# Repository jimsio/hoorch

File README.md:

an educational multimedia box

HOORCH is a multimedia box for primary school students. HOORCH is a dialect saying that means something like "listen up!".
It consists of a Raspberry Pi 3A+ , 6 RFID-Readers, a microphone, speakers and several LEDs and buttons. It is housed in a laser cutted box with a transparent board top.
We currently have 6 games:
* a storytelling game, where kids can record stories which are then stored for their specific character
* a calculating game
* a game for learning english animal names
* an animal voice guessing game
* an animal orchestra game for learning the animal voices
* a game for learning the parts of a modern instrumental song (e.g. bass line, hi-hat, snare, kick, melody)

Folders:
* . : python program, installation file (installer.sh), 
* [data](data): audio files
* [pcb](pcb): schematics, made with KiCad
* [graphics](graphics): laser cutter files for box, figures. vinylcutter files for cards, graphic files for animal stickers
* [docs](docs): documentation

HOORCH was developed at the University for Teacher Training (PH Wien) in Vienna, Austria.

Also visit our website:
(http://hoorch.phwien.ac.at)

# Installation

see [docs](docs)

# License

Licenced under the CC-BY-NC-SA 4.0 license

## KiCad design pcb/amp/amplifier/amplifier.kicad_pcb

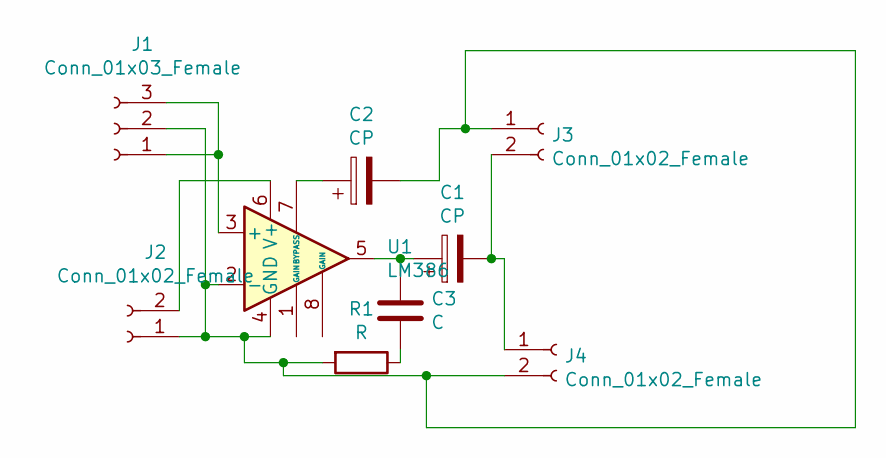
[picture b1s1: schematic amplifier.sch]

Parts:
C1: CP; CP_Radial_D10.0mm_P3.80mm
C2: CP; CP_Radial_D5.0mm_P2.50mm
C3: C; C_Disc_D4.3mm_W1.9mm_P5.00mm
J1: Conn_01x03_Female; PinHeader_1x03_P2.54mm_Vertical
J2, J3, J4: Conn_01x02_Female; PinHeader_1x02_P2.54mm_Vertical
R1: R; R_Axial_DIN0207_L6.3mm_D2.5mm_P10.16mm_Horizontal
U1: LM386; DIP-8_W7.62mm

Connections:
unnamed: C1.1, C3.1, U1.5
unnamed: C1.2, J3.2, J4.1
unnamed: C2.1, U1.7 (BYPASS)
unnamed: C2.2, J1.2, J2.1, J3.1, J4.2, R1.2, U1.2 (-), U1.4 (GND)
unnamed: C3.2, R1.1
unnamed: J1.1, J1.3, U1.3 (+)
unnamed: J2.2, U1.6 (V+)

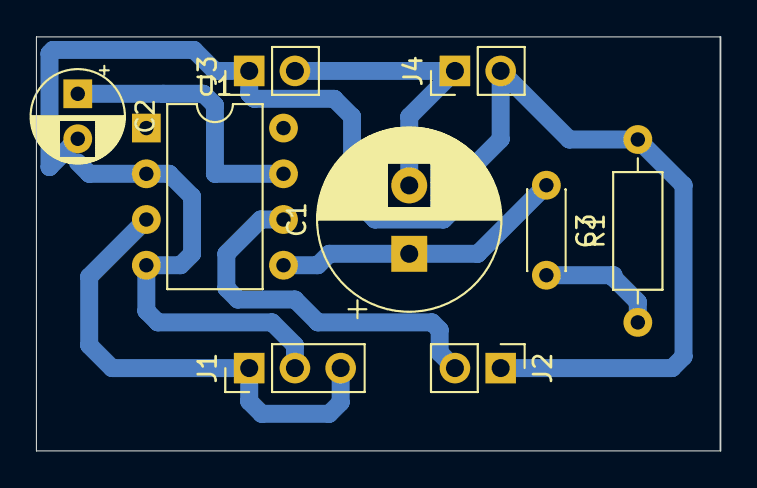
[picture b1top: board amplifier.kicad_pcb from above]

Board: 2 copper layers, 38.0 x 23.0 mm, 9 parts (0 on the bottom side), 7 nets.

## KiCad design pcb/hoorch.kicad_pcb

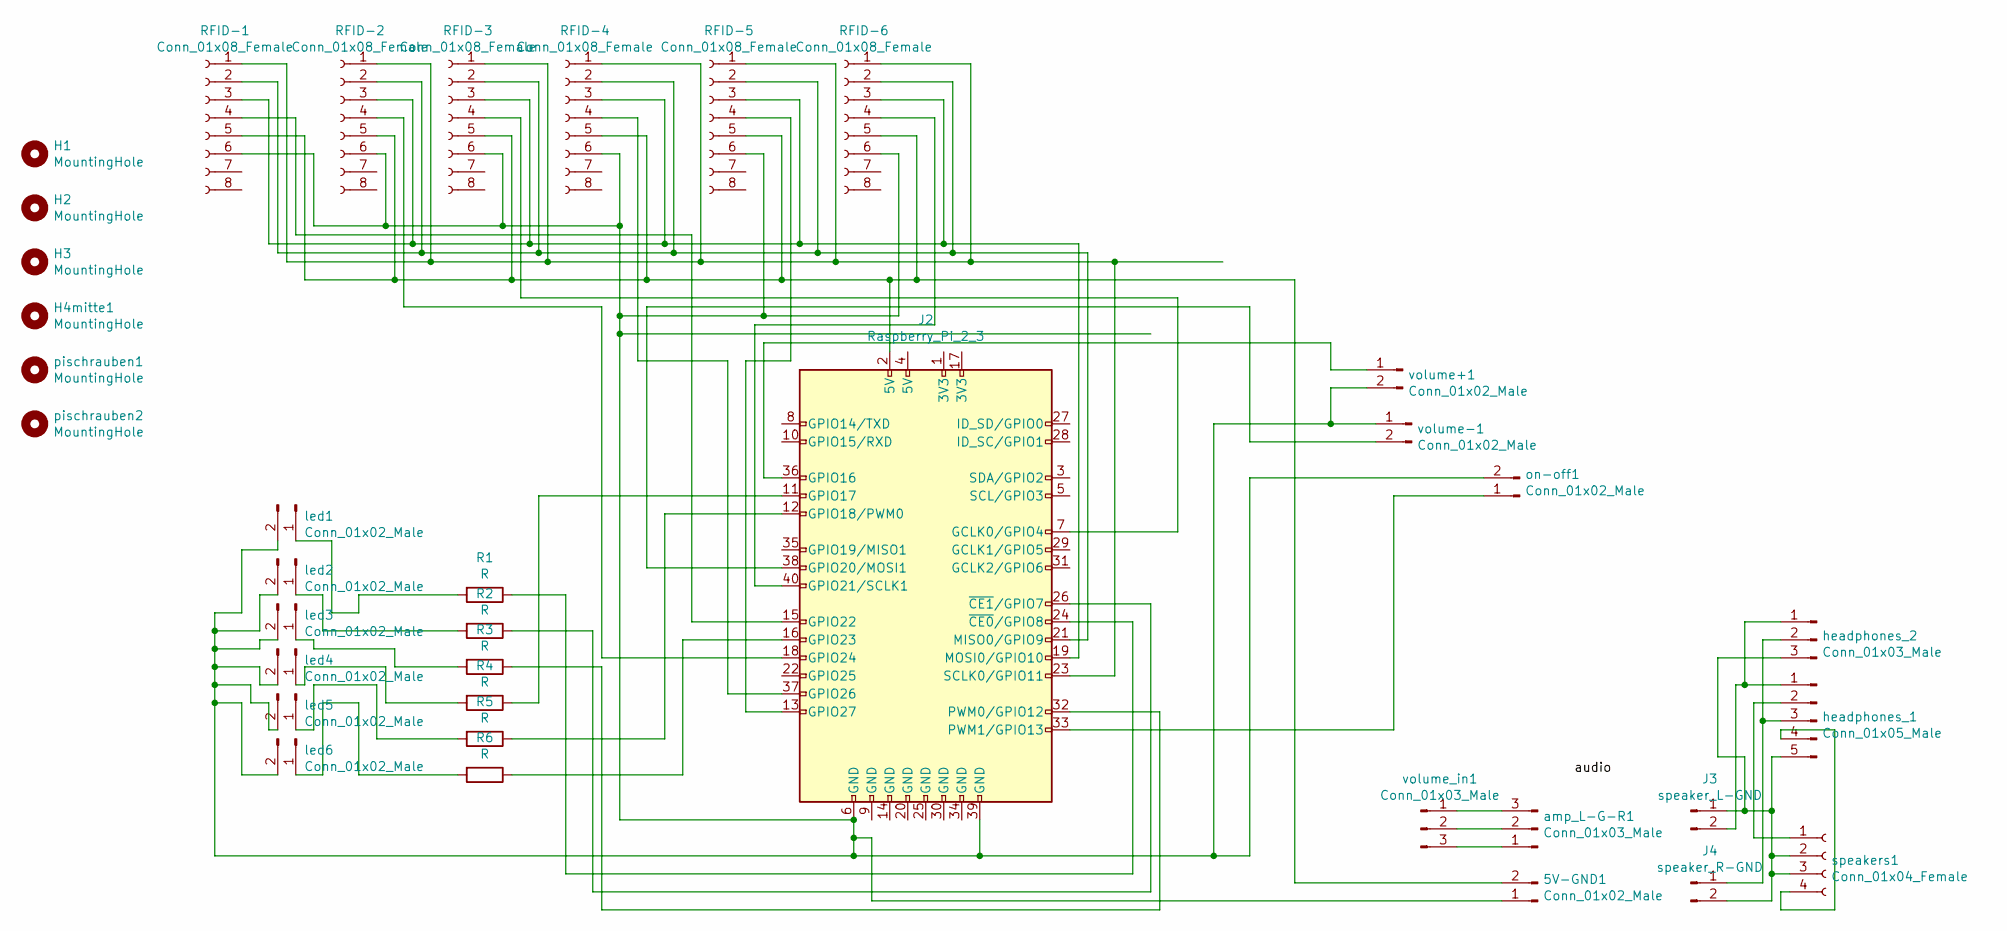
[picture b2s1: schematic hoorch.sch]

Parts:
5V-GND1: Conn_01x02_Male; PinHeader_1x02_P2.54mm_Vertical
H1, H2, H3: MountingHole; MountingHole_4.3mm_M4
H4mitte1: MountingHole; MountingHole_6.4mm_M6
J2: Raspberry_Pi_2_3; PinSocket_2x20_P2.54mm_Vertical
J3: speaker_L-GND; PinSocket_1x02_P2.54mm_Vertical
J4: speaker_R-GND; PinSocket_1x02_P2.54mm_Vertical
R1, R2, R3, R4, R5, R6: R; R_Axial_DIN0204_L3.6mm_D1.6mm_P5.08mm_Vertical
RFID-1, RFID-2, RFID-3, RFID-4, RFID-5, RFID-6: Conn_01x08_Female; PinSocket_1x08_P2.54mm_Vertical
amp_L-G-R1: Conn_01x03_Male; PinHeader_1x03_P2.54mm_Vertical
headphones_1: Conn_01x05_Male; PinHeader_1x05_P2.54mm_Vertical
headphones_2: Conn_01x03_Male; PinHeader_1x03_P2.54mm_Vertical
led1, led2, led3, led4, led5, led6: Conn_01x02_Male; PinSocket_1x02_P2.54mm_Vertical
on-off1: Conn_01x02_Male; PinSocket_1x02_P2.54mm_Vertical
pischrauben1, pischrauben2: MountingHole; MountingHole_3.2mm_M3
speakers1: Conn_01x04_Female; JST_EH_B04B-EH-A_1x04_P2.50mm_Vertical
volume+1: Conn_01x02_Male; PinSocket_1x02_P2.54mm_Vertical
volume-1: Conn_01x02_Male; PinSocket_1x02_P2.54mm_Vertical
volume_in1: Conn_01x03_Male; PinSocket_1x03_P2.54mm_Vertical

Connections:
unnamed: 5V-GND1.1, J2.6 (GND), J2.39 (GND), RFID-1.6, RFID-2.6, RFID-3.6, RFID-4.6, RFID-5.6, RFID-6.6, led1.2, led2.2, led3.2, led4.2, led5.2, led6.2, on-off1.2, volume+1.2, volume-1.1
unnamed: 5V-GND1.2, J2.2 (5V), RFID-1.5, RFID-2.5, RFID-3.5, RFID-4.5, RFID-5.5, RFID-6.5
unnamed: J2.7 (GCLK0/GPIO4), RFID-3.4
unnamed: J2.11 (GPIO17), R4.1
unnamed: J2.12 (GPIO18/PWM0), R5.1
unnamed: J2.13 (GPIO27), RFID-5.4
unnamed: J2.15 (GPIO22), RFID-1.4
unnamed: J2.16 (GPIO23), R6.1
unnamed: J2.18 (GPIO24), RFID-2.4
unnamed: J2.19 (MOSI0/GPIO10), RFID-1.3, RFID-2.3, RFID-3.3, RFID-4.3, RFID-5.3, RFID-6.3
unnamed: J2.21 (MISO0/GPIO9), RFID-1.2, RFID-2.2, RFID-3.2, RFID-4.2, RFID-5.2, RFID-6.2
unnamed: J2.23 (SCLK0/GPIO11), RFID-1.1, RFID-2.1, RFID-3.1, RFID-4.1, RFID-5.1, RFID-6.1
unnamed: J2.24 (~CE0~/GPIO8), R1.1
unnamed: J2.26 (~CE1~/GPIO7), R2.1
unnamed: J2.32 (PWM0/GPIO12), R3.1
unnamed: J2.33 (PWM1/GPIO13), on-off1.1
unnamed: J2.36 (GPIO16), volume+1.1
unnamed: J2.37 (GPIO26), RFID-4.4
unnamed: J2.38 (GPIO20/MOSI1), volume-1.2
unnamed: J2.40 (GPIO21/SCLK1), RFID-6.4
unnamed: J3.1, J4.2, headphones_1.5, headphones_2.3, speakers1.2, speakers1.3
unnamed: J3.2, headphones_1.1, headphones_2.1
unnamed: J4.1, headphones_1.3, headphones_2.2
unnamed: R1.2, led1.1
unnamed: R2.2, led2.1
unnamed: R3.2, led3.1
unnamed: R4.2, led4.1
unnamed: R5.2, led5.1
unnamed: R6.2, led6.1
unnamed: amp_L-G-R1.1, volume_in1.3
unnamed: amp_L-G-R1.2, volume_in1.2
unnamed: amp_L-G-R1.3, volume_in1.1
unnamed: headphones_1.2, speakers1.1
unnamed: headphones_1.4, speakers1.4

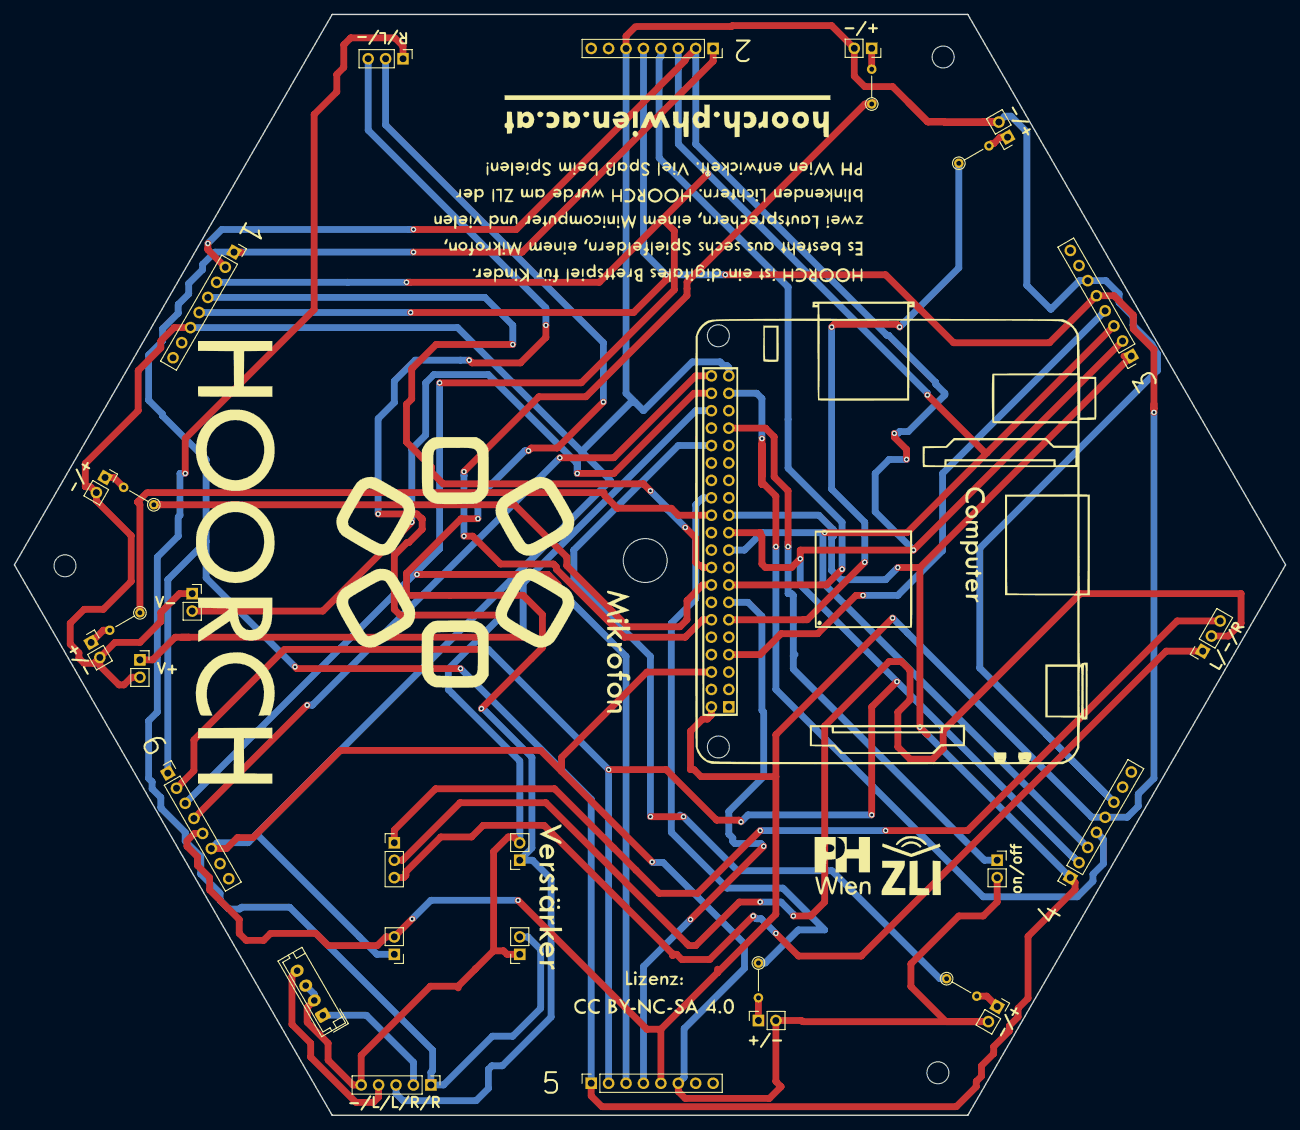
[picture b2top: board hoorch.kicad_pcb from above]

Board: 2 copper layers, 185.3 x 160.5 mm, 36 parts (1 on the bottom side), 34 nets.

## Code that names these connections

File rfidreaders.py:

#!/usr/bin/env python3
# -*- coding: UTF8 -*-

import time
import threading
import os
#import unicodedata
import board
import busio
from adafruit_pn532.spi import PN532_SPI
from adafruit_pn532.adafruit_pn532 import MIFARE_CMD_AUTH_B
#import digitalio
from digitalio import DigitalInOut
import ndef
import audio

# gpio belegung
# Reader 1: Pin18 - GPIO24
# Reader 2: Pin15 - GPIO22
# Reader 3: Pin7 - GPIO4
# Reader 4: Pin37 - GPIO26
# Reader 5: Pin13 - GPIO27
# Reader 6: Pin36 - GPIO16
reader1_pin = DigitalInOut(board.D24)
reader2_pin = DigitalInOut(board.D22)
reader3_pin = DigitalInOut(board.D4)
reader4_pin = DigitalInOut(board.D26)
reader5_pin = DigitalInOut(board.D27)
reader6_pin = DigitalInOut(board.D16)

readers = []
tags = []
timer = [0, 0, 0, 0, 0, 0]

figures_db = {}  # figure database is a dictionary with tag id and tag name stored, based on predefined figure_db.txt. figure_db.txt is created when configuring HOORCH for the first time (and is based on tag names in figure_ids.txt)
gamer_figures = []  # ritter, koenigin,...
animal_figures = []  # Loewe2, Elefant1, ...

endofmessage = "#"  # chr(35)

read_continuously = True
currently_reading = False

auth_key = b'\xFF\xFF\xFF\xFF\xFF\xFF'


def init():
    print("initialize the rfid readers and figure_db.txt")
    spi = busio.SPI(board.SCK, board.MOSI, board.MISO)

    readers.append(PN532_SPI(spi, reader1_pin, debug=False))
    readers.append(PN532_SPI(spi, reader2_pin, debug=False))
    readers.append(PN532_SPI(spi, reader3_pin, debug=False))
    readers.append(PN532_SPI(spi, reader4_pin, debug=False))
    readers.append(PN532_SPI(spi, reader5_pin, debug=False))
    readers.append(PN532_SPI(spi, reader6_pin, debug=False))

    for n, reader in enumerate(readers):
        # ic, ver, rev, support = reader.firmware_version
        # print('Found Reader '+str(n)+' with firmware version: {0}.{1}'.format(ver, rev, support))
        reader.SAM_configuration()
        print('Initialized and configured RFID/NFC reader '+str(n+1))
        tags.append(None)
        time.sleep(0.03)

    # init figure db
    path = "./figure_db.txt"

    if os.path.exists(path):
        with open(path, mode="r", encoding="utf-8") as file:
            figures_id_name = file.readlines()
        
        section = 0

        for uid_name in figures_id_name:
            # empty line means section change
            if uid_name.startswith(";"):
                section += 1
            else:
                (key, val) = uid_name.split(";")
                figures_db[key] = val[:val.find("\n")]

                if section == 2:
                    gamer_figures.append(
                        uid_name[uid_name.find(";")+1:uid_name.find("\n")])
                elif section == 3:
                    animal_figures.append(
                        uid_name[uid_name.find(";")+1:uid_name.find("\n")-1])

    continuous_read()


def continuous_read():
    
    global currently_reading

    for index, r in enumerate(readers):

        mifare = False

        currently_reading = True

        tag_uid = r.read_passive_target(timeout=0.2)
        
        if tag_uid:
            # convert byte_array tag_uid to string id_readable (i.e. 4-7-26-160)
            id_readable = ""
            for counter, number in enumerate(tag_uid):
                if counter < 4:
                    id_readable += str(number)+"-"
                else:
                    id_readable = id_readable[:-1]
                    break

            # mifare id has minus at the end, remove it here
            if id_readable.endswith("-"):
                id_readable = id_readable[:-1]
                mifare = True

            # check if tag id in figure db
            try:
                tag_name = figures_db[id_readable]

            # id_readable is not in figures_db
            except KeyError:
                
                if mifare:
                    tag_name = read_from_mifare(r, tag_uid)
                else:
                    tag_name = read_from_ntag2(r)

                # power down to safe energy, breaks readers?
                r.power_down()
                
                if tag_name == "#error#":
                    continue

                currently_reading = False

                #if tag_name is empty, use id_readable
                if not tag_name:
                    #print("tag is empty, use id_readable")
                    tag_name = id_readable

                # if a figure (i.e. Loewe0 or koenigin) from another game (i.e. as a replacement of a lost one) that is already defined in this game is used
                # add another key value pair to the figures_db database
                elif tag_name in figures_db:
                    figures_db[id_readable] = tag_name       

                else:
                    # else set the unknown figure as a gamer figure with read tag_name
            
                    if tag_name not in gamer_figures:
                        gamer_figures.append(tag_name)
                        print(
                            "added new unknown gamer figure to the temporary gamer_figure list")
                    else:
                        pass
                        #print("unknown gamer figure already in temporary gamer_figure list")

        else:
            tag_name = None

        # keep tags in array for 1 seconds to even out reading errors
        if tag_name is None and timer[index] < time.time():
            tags[index] = tag_name  # None
            timer[index] = 0  # reset timer to 0

        if tag_name is not None:
            timer[index] = time.time()+1
            tags[index] = tag_name
        
        #sleep for 0.2 seconds between readers to avoid heavy power load
        time.sleep(0.2)

    print(tags)

    if read_continuously:
        #only read when not playing or recording audio - shouldnt be done, need it for ending recording
        #while ('play' or 'rec') in subprocess.run(['ps', 'ax'], stdout=subprocess.PIPE).stdout.decode('utf-8'):
            #time.sleep(0.2)

        threading.Timer(0.02, continuous_read).start()
        
def read_from_mifare(reader, tag_uid):
    read_data = bytearray(0)
    
    try:
        #read 16 bytes from blocks 4 and 5
        for i in range(4, 6):
            #print("Authenticating block "+str(i))
                authenticated = reader.mifare_classic_authenticate_block(tag_uid, i, MIFARE_CMD_AUTH_B, auth_key)
                if not authenticated:
                    print("Authentication failed!")
                # Read blocks
                read_data.extend(reader.mifare_classic_read_block(i))
        
        to_decode = read_data[2:read_data.find(b'\xfe')]
        return list(ndef.message_decoder(to_decode))[0].text
    
    except TypeError:
        print("Error while reading RFID-tag content. Tag was probably removed before reading was completed.")
        # Die Figur konnte nicht erkannt werden. Lass sie länger auf dem Feld stehen.
        audio.play_full("TTS", 199)

        return "#error#"
    
    except ndef.record.DecodeError as e:
        print("ndeflib Error while decoding")
        print(e)

        return "error#"

def read_from_ntag2(reader):
    read_data = bytearray(0)
    
    #read 4 bytes from blocks 4-11
    try:
        for i in range(4, 12):
            read_data.extend(reader.ntag2xx_read_block(i))
        to_decode = read_data[2:read_data.find(b'\xfe')]
    
        return list(ndef.message_decoder(to_decode))[0].text

    # if tag was removed before it was properly read
    except TypeError:
        print("Error while reading RFID-tag content. Tag was probably removed before reading was completed.")
        # Die Figur konnte nicht erkannt werden. Lass sie länger auf dem Feld stehen.
        audio.play_full("TTS", 199)
        
        return "#error#"
    
    except ndef.record.DecodeError as e:
        print("ndeflib Error while decoding")
        print(e)
        
        return "error#"


#except KeyboardInterrupt:
#   for r in readers:
#    r.power_down()

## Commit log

2020-09-28 1x1 : tens a unit leds blink
2020-10-01 changed indentation
2021-01-28 added doc, pcb, graphics
2021-01-28 readme.md added picture
2021-03-01 first round beta-test update, added admin.py
2021-03-08 change answer mode animal english, tierlaute
2021-03-08 update gitignore
2021-03-08 admin update
2021-03-18 4 admin functions, update geschichte aufnehmen to correspond with damin funct to archive recorded story
2021-04-10 preparation for hoorch v4 /w i2s sound
2021-04-15 remove baudrate
2021-04-15 add git to installer
2021-04-15 add gitignore so empty folder figures to be commited
2021-04-15 update tts
2021-04-15 remove figure_db* files
2021-04-18 geschichte aufnehmen + louder volume
2021-04-22 remove power_down for saving energy, it seems to corrupt reading of some readers
2022-09-26 admin update: archive stories etc
2022-11-04 renaming magierin
    magierin instead of zauberer
    installer update
2023-01-09 update for new pcb
2023-01-09 update gitignore to upload empty test folder
2023-01-23 installer new
2023-01-30 refactor, docufiles deleted, install updated
2023-01-30 figure_dir
2023-01-30 games english
2023-01-30 lf gpio shufoff update
2023-01-30 gui removal removed
2023-01-30 syntax errors is and equals
2023-01-30 same as before
2023-01-30 format with spaces other than tabs
2023-01-30 omit tagwriter in hoorch.py for testing
2023-03-02 global variables added
2023-03-02 button debouncing added
2023-03-02 new debouncing
2023-03-02 user=root in hoorch.service
2023-03-02 added folder test
2023-03-02 add test dir in figures
2023-03-02 init test service adjustments
2023-05-04 led and hostname addons
2023-05-04 hostname do while rebuilt
2023-05-04 eld testr, record
2023-05-04 aufnahme led test
2023-05-04 removed rotate one round
2023-05-04 rec test hoorch.py
2023-05-04 add wheel
2023-05-04 rec shell false
2023-05-04 shell=False
2023-05-04 shell=true again
2023-05-04 dummy instead of wait
2023-05-04 rainbow instead of sleep
2023-05-04 leds autowrite True
2023-05-04 rec mit trim
2023-05-04 remove timeout
2023-05-04 .aif
2023-05-04 aif test with led
2023-05-04 aif with leds
2023-05-04 speakers on no auto update leds
2023-05-04 rainbow cycle faster
2023-05-04 led hoorch fix
2023-05-04 missing none
2023-05-15 remove leds, for recording test
2023-05-15 remove rfidreader
2023-05-15 added led again, test that.
2023-05-15 remove random_blinker
2023-05-15 randomtimer to blinker
2023-05-15 random timer to blink
2023-05-15 remove blinker
2023-05-15 remove global keyword
2023-05-15 optimize blinker
2023-05-15 rere
2023-05-15 set volume at start
2023-05-15 audio changed
2023-05-15 write set with tagwriter
2023-05-15 remove rotate one round, not wokring
2023-05-15 flickering because of too fast neopixel.show
2023-05-15 aufnahme switch all on with color
2023-05-15 stop continuous read for writing set
2023-05-15 continuous reed start again
2023-05-15 init outside
2023-05-15 update for new led functions
2023-05-15 remove figures without story
2023-05-15 check if story exists
2023-05-15 geschichten abspielen
2023-05-15 figure id
2023-05-15 jooo
2023-05-25 new ttts, lower start volume
2023-06-05 installer mv asoundrc
2023-09-28 added game_hoerspiele
2023-10-12 refactor, remove contiuous read from hardware init
2023-10-12 rfidreaders sleep o avoid voltage drop
2023-10-12 rfidreaders threading timer 1.4
2023-10-12 lower volume
2023-10-12 pygame set nr channels
2023-10-12 kakophonie reactivate
2023-10-12 add rotate leds 1x1
2023-10-12 remove blink
2023-10-12 leds off
2023-10-16 reader adjustments
2023-10-16 readers mifare test
2023-10-16 mifare readwrite
2023-10-16 mifare done
2023-10-16 test led+recording
2023-10-16 fix reset error
2023-10-16 test switch on with color while recording
2023-10-16 switch all on with color
2023-10-23 added helper for rec testing
2023-11-09 check if tagname empty
2023-11-09 tagname seems empty but is not check with bytearray
2023-11-09 check for empty tagname
2023-11-20 avoid simultaneous rfid-read and audio play
2023-11-27 test tagwriter with mifare
2023-11-27 volume up
2023-11-27 tagwriter x0E
2023-11-27 payload _enc
2023-11-27 enc tagwriter
2023-11-27 tagwriter writesingle
2023-11-27 prefix x0A
2024-01-11 use ndeflib
2024-01-11 hex to byte
2024-01-11 bytearray fromhex
2024-01-11 test kaka
2024-01-11 remove audio
2024-01-11 remove /x00 from prefix
2024-01-11 pprint data
2024-01-11 data2
2024-01-15 tagwriter + rfidreaders update mifare
2024-01-15 len payload
2024-01-15 bytearray convertion
2024-01-15 print data
2024-01-15 write to block
2024-01-15 send type
2024-01-15 chunks
2024-01-15 id_readable missing
2024-01-15 switch on amp
2024-01-18 refactor rfridreaders
2024-01-18 mifare block1+2
2024-01-18 write 1245 read45 only
2024-01-18 xgreater
2024-01-18 print data mifare
2024-01-18 lendata
2024-02-29 nfc out of range fix
2024-02-29 continuous read fix
2024-02-29 reader copy error fix
2024-02-29 catch typeerror
2024-02-29 tailing minus idreadable error fix
2024-02-29 fix tailing minus again
2024-02-29 refactor
2024-03-18 added server
2024-04-03 added hoerspiele to main menu
2024-04-03 hoerspiele list remove file extension
2024-04-03 test test
2024-04-03 admin update available message
2024-04-03 admin datetime fstring
2024-04-03 admin null error
2024-04-04 hoerspiele form main menu
2024-04-04 remove files from figure_dirs hoorch.py
2024-04-04 remove .mp3
2024-04-04 add hoerspiele to game_hoerspiele
2024-04-08 removed power down, added webserver.service and install script
2024-04-11 added aufnehmen from main menu
2024-04-22 led boost 0.9 brightness, espeaker fix elif rec-play from main menu
2024-04-22 readers power down
2024-04-22 elfi hoorch main mneu
2024-04-25 add main in hooorch.py
2024-04-25 comment
2024-04-29 a lot
2024-04-29 detected figure without recording
2024-04-29 return "#error#"
2024-05-22 change sleep time
2024-05-22 hoerspiele folder
2024-05-22 error handling rfid reading
2024-05-22 ndeflib error print
2024-05-29 espeak volume down
2024-05-29 write without mifare 00:00 prefix
2024-05-29 klammer
2024-05-29 clean up
